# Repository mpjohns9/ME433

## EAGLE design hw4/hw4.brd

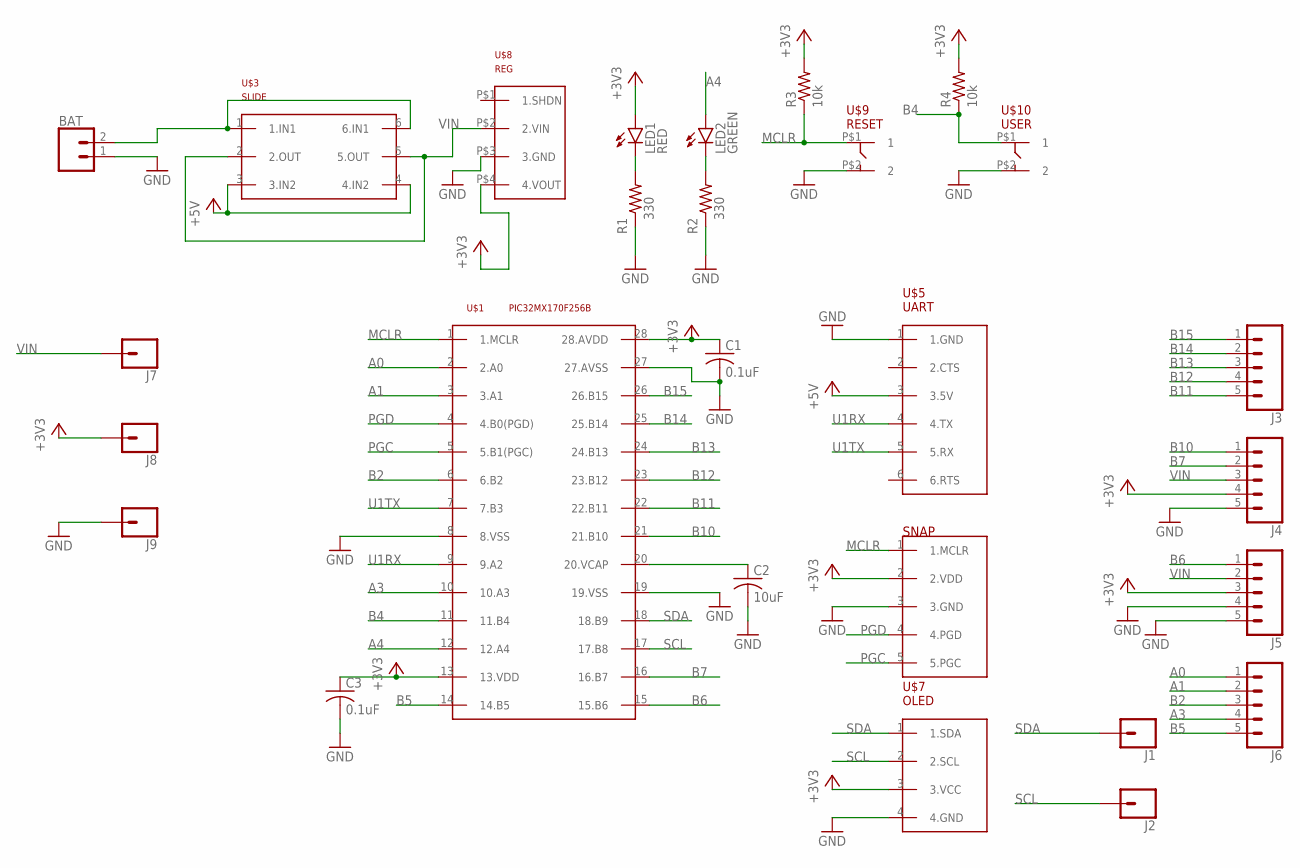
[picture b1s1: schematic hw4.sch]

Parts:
BAT: CONN_02; 1X02
C1, C3: 0.1uF; C025-024X044
C2: 10uF; C025-024X044
J1, J2, J7, J8, J9: CONN_01; 1X01
J3, J4, J5, J6: CONN_05; 1X05
LED1: RED; LED3MM
LED2: GREEN; LED3MM
R1, R2: 330; 0207/7
R3, R4: 10k; 0207/2V
U$1: PIC32MX170F256B; DIL28-3
U$3: SLIDE
U$5: UART
U$6: SNAP
U$7: OLED
U$8: REG
U$9: RESET; PUSH
U$10: USER; PUSH

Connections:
+3V3: C1.1, C3.1, J4.4, J5.3, J8.1, LED1.A, R3.2, R4.2, U$1.13 (13.VDD), U$1.28 (28.AVDD), U$6.2 (2.VDD), U$7.3 (3.VCC), U$8.P$4 (4.VOUT)
+5V: U$3.3 (3.IN2), U$3.4 (4.IN2), U$5.3 (3.5V)
A0: J6.1, U$1.2 (2.A0)
A1: J6.2, U$1.3 (3.A1)
A3: J6.4, U$1.10 (10.A3)
A4: LED2.A, U$1.12 (12.A4)
B2: J6.3, U$1.6 (6.B2)
B4: R4.1, U$1.11 (11.B4), U$10.P$1 (1)
B5: J6.5, U$1.14 (14.B5)
B6: J5.1, U$1.15 (15.B6)
B7: J4.2, U$1.16 (16.B7)
B10: J4.1, U$1.21 (21.B10)
B11: J3.5, U$1.22 (22.B11)
B12: J3.4, U$1.23 (23.B12)
B13: J3.3, U$1.24 (24.B13)
B14: J3.2, U$1.25 (25.B14)
B15: J3.1, U$1.26 (26.B15)
GND: BAT.1, C1.2, C2.2, C3.2, J4.5, J5.4, J5.5, J9.1, R1.1, R2.1, U$1.8 (8.VSS), U$1.19 (19.VSS), U$1.27 (27.AVSS), U$5.1 (1.GND), U$6.3 (3.GND), U$7.4 (4.GND), U$8.P$3 (3.GND), U$9.P$2 (2), U$10.P$2 (2)
MCLR: R3.1, U$1.1 (1.MCLR), U$6.1 (1.MCLR), U$9.P$1 (1)
unnamed: BAT.2, U$3.1 (1.IN1), U$3.6 (6.IN1)
unnamed: C2.1, U$1.20 (20.VCAP)
unnamed: LED1.K (C), R1.2
unnamed: LED2.K (C), R2.2
PGC: U$1.5 (5.B1(PGC)), U$6.5 (5.PGC)
PGD: U$1.4 (4.B0(PGD)), U$6.4 (4.PGD)
SCL: J2.1, U$1.17 (17.B8), U$7.2 (2.SCL)
SDA: J1.1, U$1.18 (18.B9), U$7.1 (1.SDA)
U1RX: U$1.9 (9.A2), U$5.4 (4.TX)
U1TX: U$1.7 (7.B3), U$5.5 (5.RX)
VIN: J4.3, J5.2, J7.1, U$3.2 (2.OUT), U$3.5 (5.OUT), U$8.P$2 (2.VIN)

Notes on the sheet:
SNAP

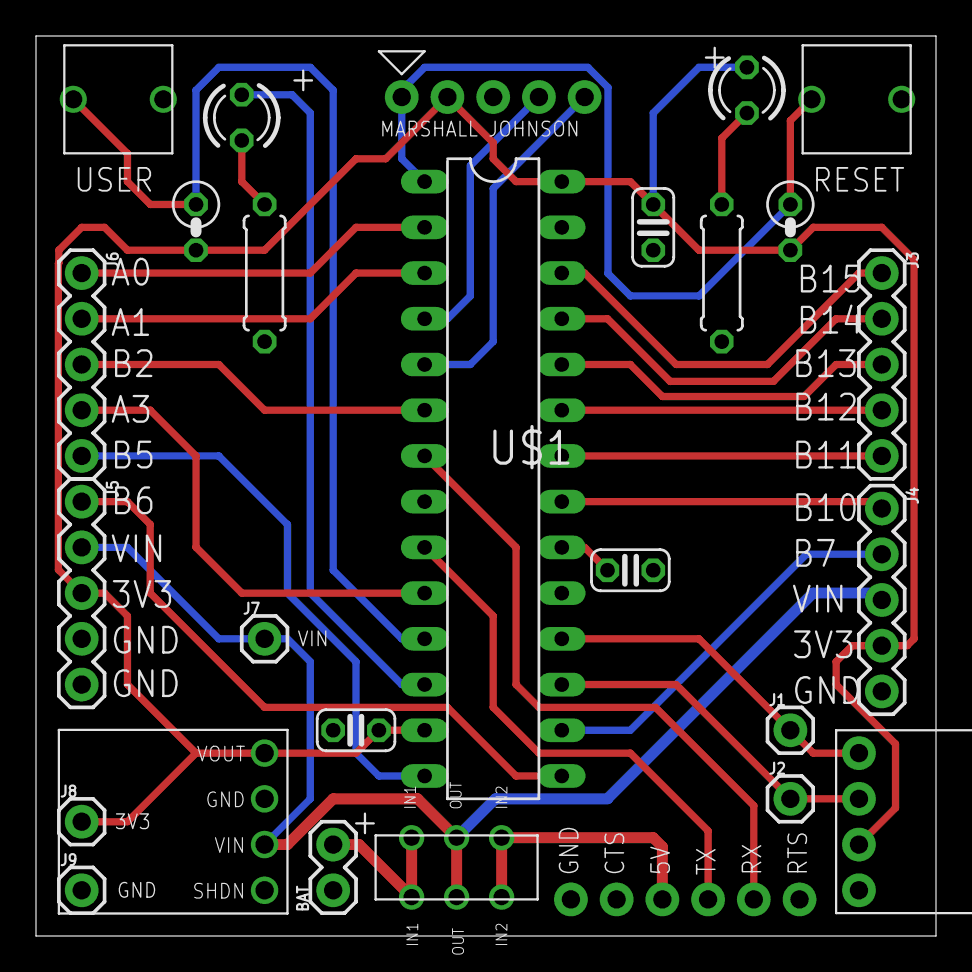
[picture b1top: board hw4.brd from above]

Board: 2 copper layers, 50.0 x 50.0 mm, 27 parts (0 on the bottom side), 30 nets.

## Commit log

2022-04-05 Set up main file
2022-04-05 Added gitignore
2022-04-05 Light blinks on button press
2022-04-05 Added circuit images
2022-04-07 Updated gitignore for hw3
2022-04-07 Added UART functionality
    Message printed to screen
2022-04-14 Completed hw4
2022-05-16 Updating files
2022-05-16 Completed hw5
2022-06-01 Completed hw6
2022-06-02 Completed hw7
2022-06-06 Completed hw8
2022-06-06 Completed hw9
2022-06-06 Completed hw10
2022-06-08 Completed hw11
2022-06-08 Added images

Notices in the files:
parts and their libraries:
SparkFun-Connectors: Licensing: Creative Commons ShareAlike 4.0 International - https://creativecommons.org/licenses/by-sa/4.0
